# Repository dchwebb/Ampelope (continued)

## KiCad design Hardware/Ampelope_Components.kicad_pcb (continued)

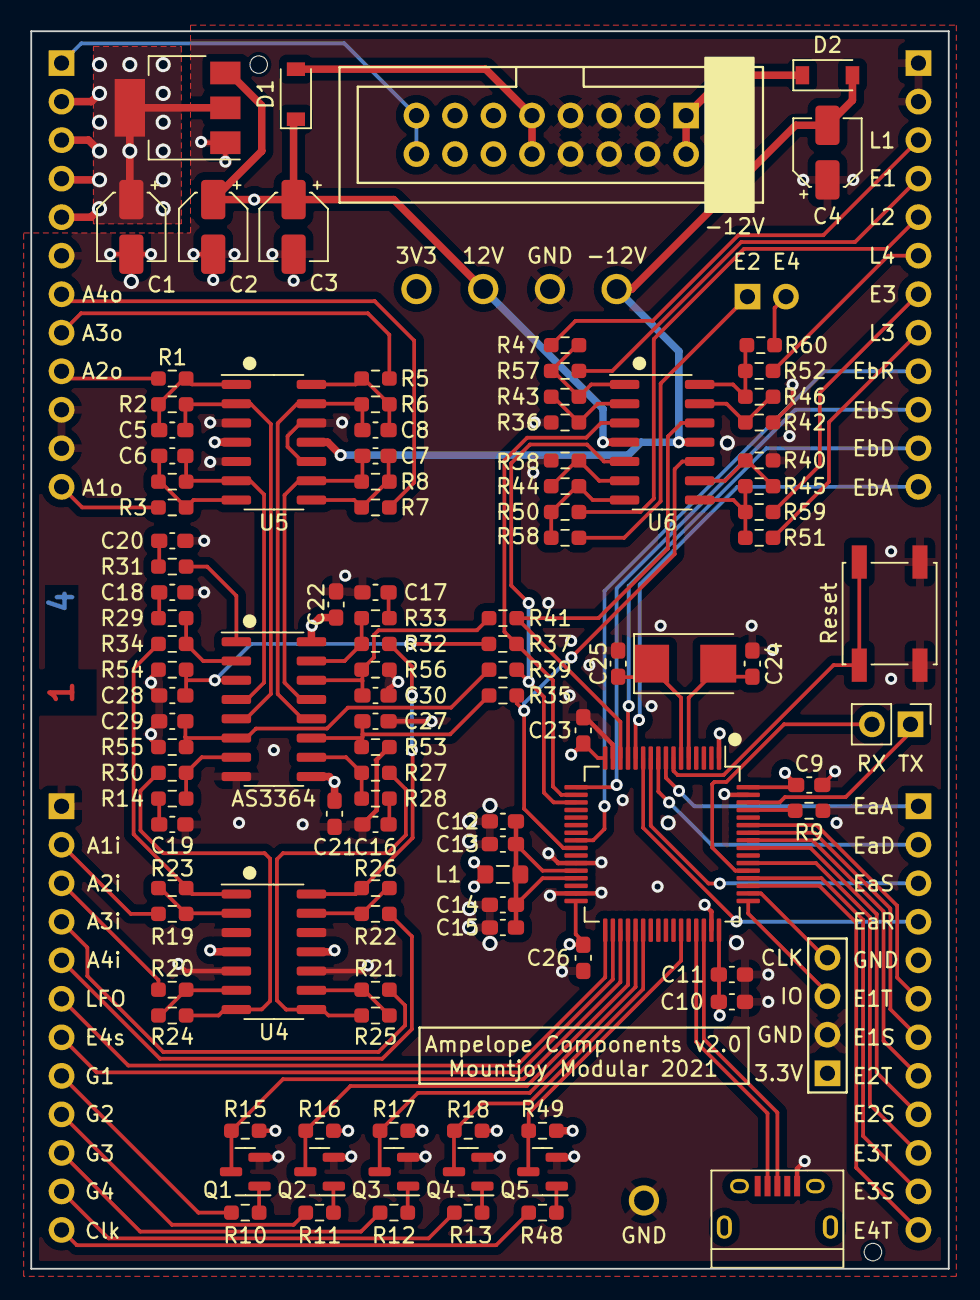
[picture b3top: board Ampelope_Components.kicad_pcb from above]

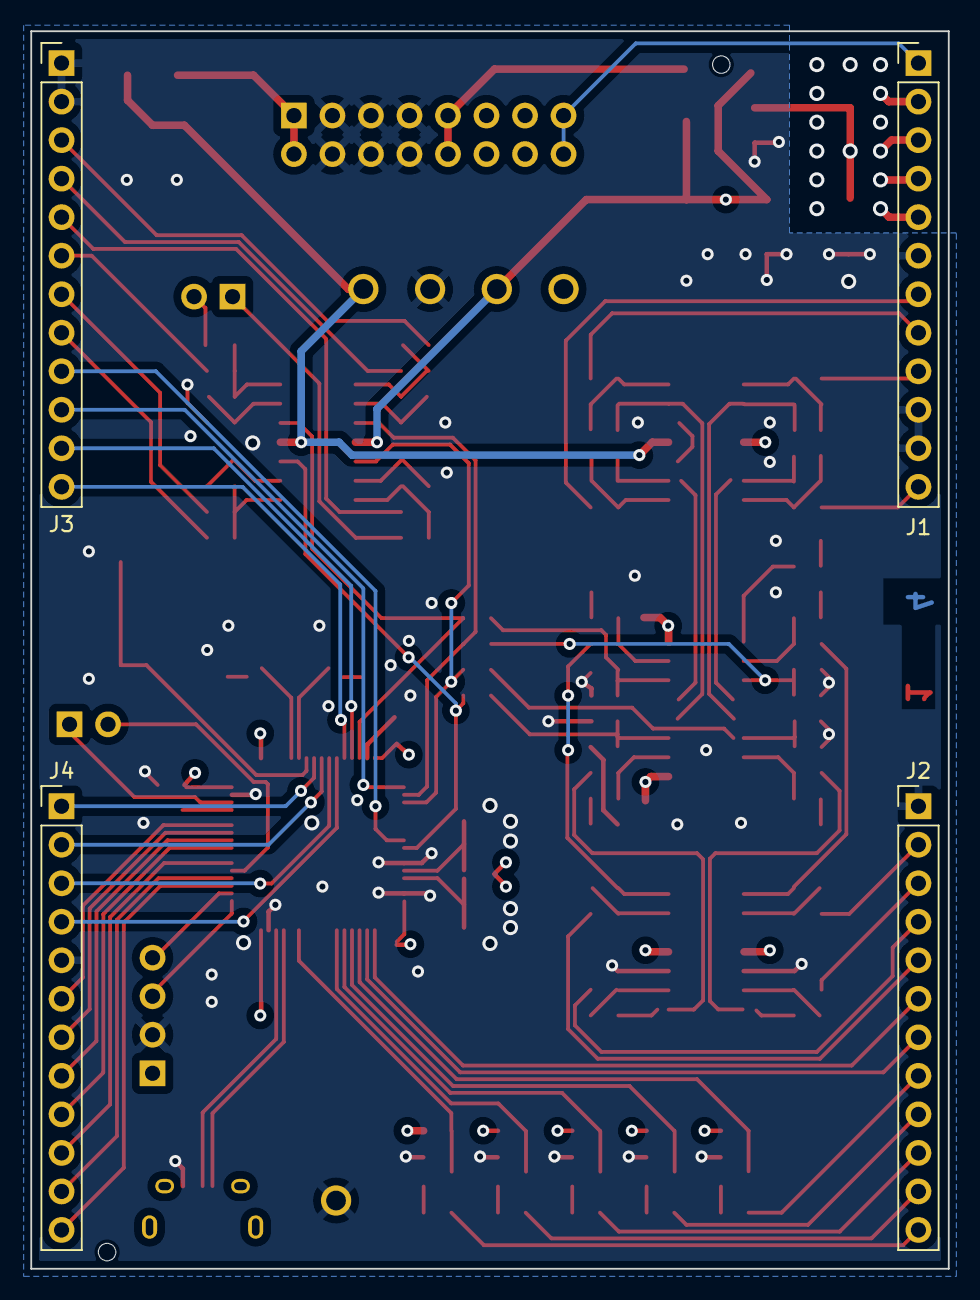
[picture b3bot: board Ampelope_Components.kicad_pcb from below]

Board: 4 copper layers, 60.5 x 81.6 mm, 123 parts (4 on the bottom side), 108 nets.

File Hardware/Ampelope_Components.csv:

"Source:","D:\Eurorack\Ampelope\Hardware\Ampelope_Components.kicad_sch"
"Date:","22/09/2021 17:17:07"
"Tool:","Eeschema (5.99.0-12348-g4b436fb86d)"
"Generator:","C:\Program Files\KiCad\5.99\bin\scripting\plugins/bom_csv_grouped_by_value_with_fp.py"
"Component Count:","121"
"Ref","Qnty","Value","Cmp name","Footprint","Description","Vendor"
"C1, C2, C3, C4, ","4","22uF","CP_Small","Capacitor_SMD:CP_Elec_4x5.8","Polarized capacitor, small symbol",""
"C5, C6, C7, C8, ","4","100pF","C_Small","Capacitor_SMD:C_0603_1608Metric_Pad1.08x0.95mm_HandSolder","Unpolarized capacitor, small symbol",""
"C9, C11, C13, C21, C22, C23, C26, ","7","100nF","C_Small","Capacitor_SMD:C_0603_1608Metric_Pad1.08x0.95mm_HandSolder","Unpolarized capacitor, small symbol",""
"C10, ","1","4.7uF","C_Small","Capacitor_SMD:C_0603_1608Metric_Pad1.08x0.95mm_HandSolder","Unpolarized capacitor, small symbol",""
"C12, C15, ","2","1uF","C_Small","Capacitor_SMD:C_0603_1608Metric_Pad1.08x0.95mm_HandSolder","Unpolarized capacitor, small symbol",""
"C14, C20, ","2","10nF","C_Small","Capacitor_SMD:C_0603_1608Metric_Pad1.08x0.95mm_HandSolder","Unpolarized capacitor, small symbol",""
"C16, C17, C18, C19, ","4","560pF","C_Small","Capacitor_SMD:C_0603_1608Metric_Pad1.08x0.95mm_HandSolder","Unpolarized capacitor, small symbol",""
"C24, C25, ","2","30pF","C_Small","Capacitor_SMD:C_0603_1608Metric_Pad1.08x0.95mm_HandSolder","Unpolarized capacitor, small symbol",""
"C27, C28, C29, C30, ","4","2.2nF","C_Small","Capacitor_SMD:C_0603_1608Metric_Pad1.08x0.95mm_HandSolder","Unpolarized capacitor, small symbol",""
"D1, D2, ","2","1N5819","1N5819","Diode_SMD:D_SOD-123","40V 1A Schottky Barrier Rectifier Diode, DO-41",""
"FID1, ","1","4_Layer_Marker","Fiducial","Custom_Footprints:4_Layer_Markers","Fiducial Marker",""
"J1, J2, J3, J4, ","4","Conn_01x12_Male","Conn_01x12_Male","Connector_PinHeader_2.54mm:PinHeader_1x12_P2.54mm_Vertical","Generic connector, single row, 01x12, script generated (kicad-library-utils/schlib/autogen/connector/)",""
"J5, ","1","Eurorack_16_pin_power","Eurorack_16_pin_power","Custom_Footprints:Eurorack_16_pin_header","",""
"J6, J9, ","2","Conn_01x02_Male","Conn_01x02_Male","Connector_PinHeader_2.54mm:PinHeader_1x02_P2.54mm_Vertical","Generic connector, single row, 01x02, script generated (kicad-library-utils/schlib/autogen/connector/)",""
"J7, ","1","SWD_Header","Conn_01x04_Male","Custom_Footprints:SWD_header","Generic connector, single row, 01x04, script generated (kicad-library-utils/schlib/autogen/connector/)",""
"J8, ","1","USB_B_Micro","USB_B_Micro","Custom_Footprints:USB_Micro-B_Amphenol","USB Micro Type B connector",""
"L1, ","1","L_Small","L_Small","Inductor_SMD:L_0805_2012Metric_Pad1.05x1.20mm_HandSolder","Inductor, small symbol",""
"Q1, Q2, Q3, Q4, Q5, ","5","MMBT3906","MMBT3906","Package_TO_SOT_SMD:SOT-23","-0.2A Ic, -40V Vce, Small Signal PNP Transistor, SOT-23",""
"R1, R3, R5, R7, R47, R50, R51, R52, R57, R58, R59, R60, ","12","1k","R_Small","Resistor_SMD:R_0603_1608Metric_Pad0.98x0.95mm_HandSolder","Resistor, small symbol",""
"R2, R4, R6, R8, R27, R30, R32, R34, ","8","30k","R_Small","Resistor_SMD:R_0603_1608Metric_Pad0.98x0.95mm_HandSolder","Resistor, small symbol",""
"R9, ","1","100k","R_Small","Resistor_SMD:R_0603_1608Metric_Pad0.98x0.95mm_HandSolder","Resistor, small symbol",""
"R10, R11, R12, R13, R15, R16, R17, R18, R43, R44, R45, R46, R48, R49, ","14","4k7","R_Small","Resistor_SMD:R_0603_1608Metric_Pad0.98x0.95mm_HandSolder","Resistor, small symbol",""
"R14, R28, R29, R33, ","4","510R","R_Small","Resistor_SMD:R_0603_1608Metric_Pad0.98x0.95mm_HandSolder","Resistor, small symbol",""
"R19, R20, R21, R22, R23, R24, R25, R26, R53, R54, R55, R56, ","12","10k","R_Small","Resistor_SMD:R_0603_1608Metric_Pad0.98x0.95mm_HandSolder","Resistor, small symbol",""
"R31, ","1","100R","R_Small","Resistor_SMD:R_0603_1608Metric_Pad0.98x0.95mm_HandSolder","Resistor, small symbol",""
"R35, R37, R39, R41, ","4","6k8","R_Small","Resistor_SMD:R_0603_1608Metric_Pad0.98x0.95mm_HandSolder","Resistor, small symbol",""
"R36, R38, R40, R42, ","4","3k3","R_Small","Resistor_SMD:R_0603_1608Metric_Pad0.98x0.95mm_HandSolder","Resistor, small symbol",""
"RESET1, ","1","SW_Push","SW_Push","Custom_Footprints:SW_SPST_EVQQ2","Push button switch, generic, two pins",""
"TP1, TP2, TP3, TP4, TP5, ","5","TestPoint","TestPoint","Custom_Footprints:1.3mm_Test_Point","test point",""
"U1, ","1","STM32G431RB","STM32G431RB","Package_QFP:LQFP-64_10x10mm_P0.5mm","ARM Cortex-M4 MCU, 128KB flash, 32KB RAM, 170MHz, 1.8-3.6V, 50 GPIO, LQFP-64",""
"U2, ","1","AS3364","SSI2164","Package_SO:SOIC-16_3.9x9.9mm_P1.27mm","Quad VCA, SOIC-16",""
"U3, ","1","LM1117-3.3","LM1117-3.3","Package_TO_SOT_SMD:SOT-223-3_TabPin2","800mA Low-Dropout Linear Regulator, 3.3V fixed output, TO-220/TO-252/TO-263/SOT-223",""
"U4, U5, U6, ","3","TL074","TL074","Package_SO:SOIC-14_3.9x8.7mm_P1.27mm","Quad Low-Noise JFET-Input Operational Amplifiers, DIP-14/SOIC-14",""
"Y1, ","1","8MHz 20pF","Crystal","Crystal:Crystal_SMD_0603-2Pin_6.0x3.5mm","Two pin crystal",""

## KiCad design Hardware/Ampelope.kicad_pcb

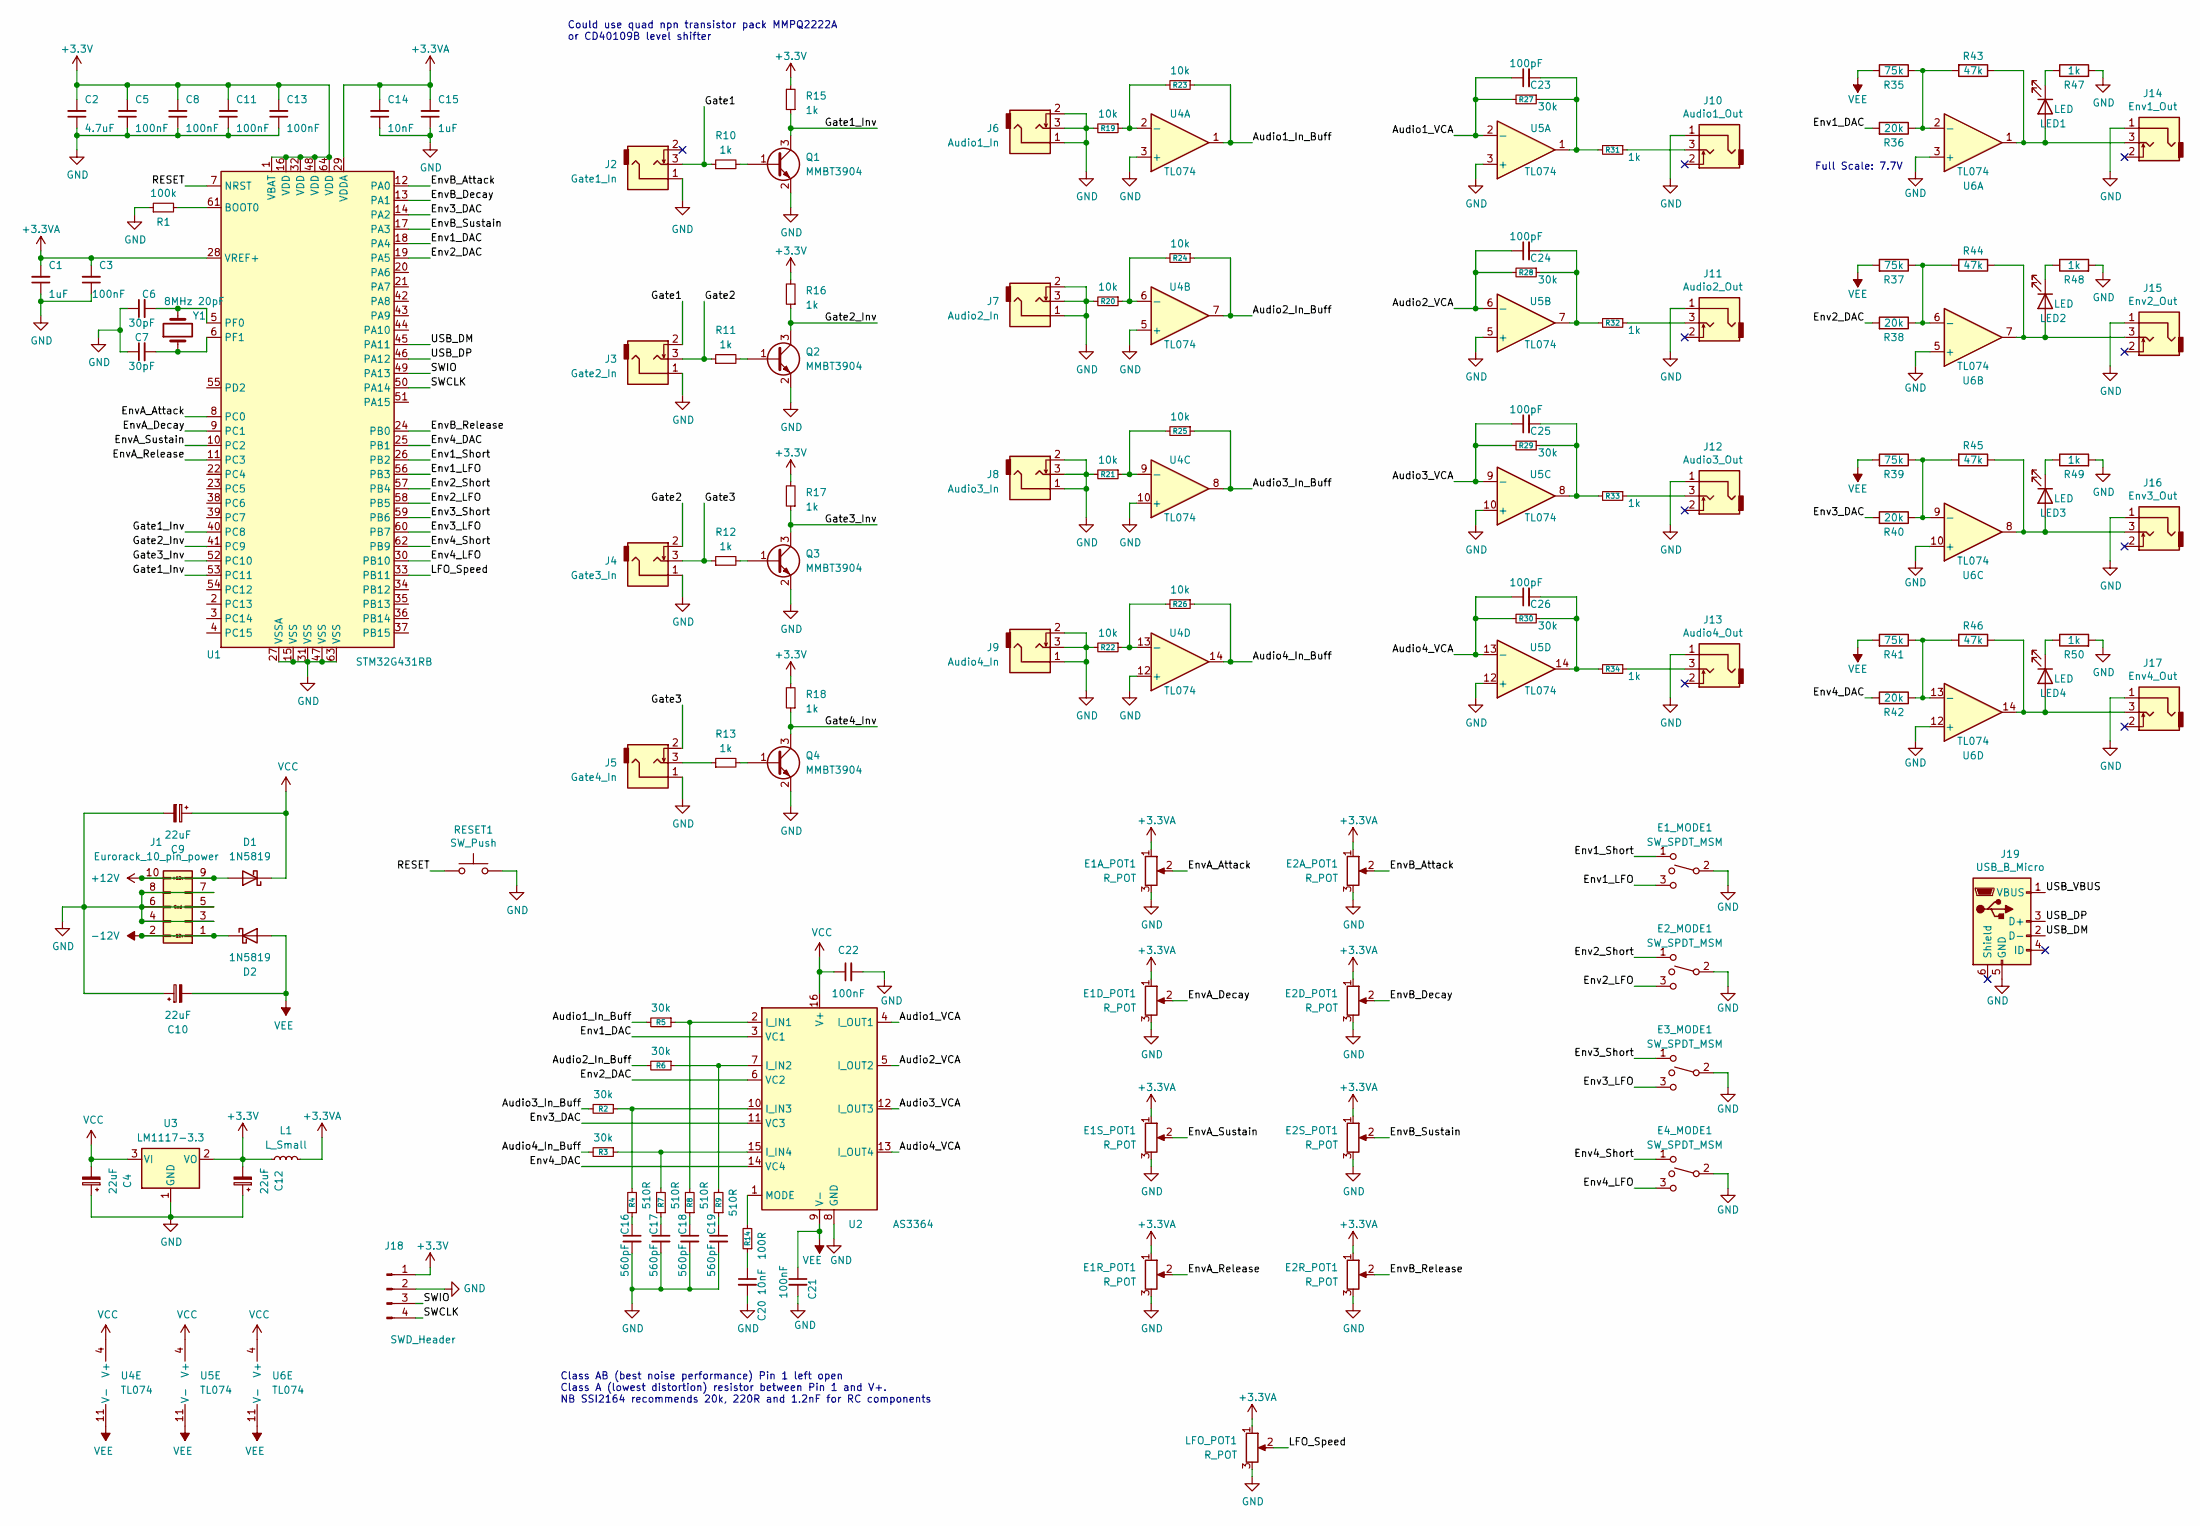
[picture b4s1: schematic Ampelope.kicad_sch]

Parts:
C1, C15: 1uF; C_0603_1608Metric_Pad1.08x0.95mm_HandSolder
C2: 4.7uF; C_0603_1608Metric_Pad1.08x0.95mm_HandSolder
C3, C5, C8, C11, C13: 100nF; C_0603_1608Metric_Pad1.08x0.95mm_HandSolder
C4, C9, C10, C12: 22uF; CP_Elec_4x5.8
C6, C7: 30pF; C_0603_1608Metric_Pad1.08x0.95mm_HandSolder
C14: 10nF; C_0603_1608Metric_Pad1.08x0.95mm_HandSolder
C16, C17, C18, C19: 560pF; C_0603_1608Metric_Pad1.08x0.95mm_HandSolder; Part_Number C84721
C20: 10nF; C_0603_1608Metric_Pad1.08x0.95mm_HandSolder; Part_Number C57112
C21, C22: 100nF; C_0603_1608Metric_Pad1.08x0.95mm_HandSolder; Part_Number C84721
C23, C24, C25, C26: 100pF; C_0603_1608Metric_Pad1.08x0.95mm_HandSolder
D1, D2: 1N5819; D_SOD-123
E1A_POT1, E1D_POT1, E1R_POT1, E1S_POT1, E2A_POT1, E2D_POT1, E2R_POT1, E2S_POT1: R_POT; Alpha_9mm_Potentiometer_Aligned
E1_MODE1, E2_MODE1, E3_MODE1, E4_MODE1: SW_SPDT_MSM; SPDT_SubMiniature_Aligned
J1: Eurorack_10_pin_power; Eurorack_10_pin_header
J2: Gate1_In; THONKICONN_hole
J3: Gate2_In; THONKICONN_hole
J4: Gate3_In; THONKICONN_hole
J5: Gate4_In; THONKICONN_hole
J6: Audio1_In; THONKICONN_hole
J7: Audio2_In; THONKICONN_hole
J8: Audio3_In; THONKICONN_hole
J9: Audio4_In; THONKICONN_hole
J10: Audio1_Out; THONKICONN_hole
J11: Audio2_Out; THONKICONN_hole
J12: Audio3_Out; THONKICONN_hole
J13: Audio4_Out; THONKICONN_hole
J14: Env1_Out; THONKICONN_hole
J15: Env2_Out; THONKICONN_hole
J16: Env3_Out; THONKICONN_hole
J17: Env4_Out; THONKICONN_hole
J18: SWD_Header; SWD_header
J19: USB_B_Micro; USB_Micro-B_Amphenol
L1: L_Small; L_0805_2012Metric_Pad1.05x1.20mm_HandSolder
LED1, LED2, LED3, LED4: LED; LED_D3.0mm
LFO_POT1: R_POT; Alpha_9mm_Potentiometer_Aligned
Q1, Q2, Q3, Q4: MMBT3904; SOT-23
R1: 100k; R_0603_1608Metric_Pad0.98x0.95mm_HandSolder
R2, R3, R5, R6, R27, R28, R29, R30: 30k; R_0603_1608Metric_Pad0.98x0.95mm_HandSolder; Part_Number C22984
R4, R7, R8, R9: 510R; R_0603_1608Metric_Pad0.98x0.95mm_HandSolder; Part_Number C23193
R10, R11, R12, R13, R15, R16, R17, R18: 1k; R_0603_1608Metric_Pad0.98x0.95mm_HandSolder
R14: 100R; R_0603_1608Metric_Pad0.98x0.95mm_HandSolder; Part_Number C22775
R19, R20, R21, R22, R23, R24, R25, R26: 10k; R_0603_1608Metric_Pad0.98x0.95mm_HandSolder; Part_Number C22984
R31, R32, R33, R34: 1k; R_0603_1608Metric_Pad0.98x0.95mm_HandSolder; Part_Number C22984
R35, R37, R39, R41: 75k; R_0603_1608Metric_Pad0.98x0.95mm_HandSolder; Part_Number C23231
R36, R38, R40, R42: 20k; R_0603_1608Metric_Pad0.98x0.95mm_HandSolder; Part_Number C25803
R43, R44, R45, R46: 47k; R_0603_1608Metric_Pad0.98x0.95mm_HandSolder; Part_Number C25819
R47, R48, R49, R50: 1k; R_0603_1608Metric_Pad0.98x0.95mm_HandSolder; Part_Number C25819
RESET1: SW_Push; SW_PUSH_6mm_aligned
U1: STM32G431RB; LQFP-64_10x10mm_P0.5mm
U2: AS3364; SOIC-16_3.9x9.9mm_P1.27mm
U3: LM1117-3.3; SOT-223-3_TabPin2
U4, U5, U6: TL074; SOIC-14_3.9x8.7mm_P1.27mm
Y1: 8MHz 20pF; Crystal_SMD_5032-2Pin_5.0x3.2mm_HandSoldering; Part_Number C115962

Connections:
+3.3VA: C1.2, C3.2, C14.2, C15.2, E1A_POT1.1, E1D_POT1.1, E1R_POT1.1, E1S_POT1.1, E2A_POT1.1, E2D_POT1.1, E2R_POT1.1, E2S_POT1.1, L1.2, LFO_POT1.1, U1.28 (VREF+), U1.29 (VDDA)
+3V3: C2.2, C5.2, C8.2, C11.2, C12.2, C13.2, J18.1, L1.1, R15.2, R16.2, R17.2, R18.2, U1.1 (VBAT), U1.16 (VDD), U1.32 (VDD), U1.48 (VDD), U1.64 (VDD), U3.2 (VO)
+12V: D1.2 (A), J1.9, J1.10
-12V: D2.1 (K), J1.1, J1.2
/Audio1_In_Buff: R5.2, R23.1, U4.1
/Audio1_VCA: C23.1, R27.2, U2.4 (I_OUT1), U5.2 (-)
/Audio2_In_Buff: R6.2, R24.1, U4.7
/Audio2_VCA: C24.1, R28.2, U2.5 (I_OUT2), U5.6 (-)
/Audio3_In_Buff: R2.2, R25.1, U4.8
/Audio3_VCA: C25.1, R29.2, U2.12 (I_OUT3), U5.9 (-)
/Audio4_In_Buff: R3.2, R26.1, U4.14
/Audio4_VCA: C26.1, R30.2, U2.13 (I_OUT4), U5.13 (-)
/Env1_DAC: R36.2, U1.18 (PA4), U2.3 (VC1)
/Env1_LFO: E1_MODE1.3, U1.56 (PB3)
/Env1_Short: E1_MODE1.1, U1.26 (PB2)
/Env2_DAC: R38.2, U1.19 (PA5), U2.6 (VC2)
/Env2_LFO: E2_MODE1.3, U1.58 (PB5)
/Env2_Short: E2_MODE1.1, U1.57 (PB4)
/Env3_DAC: R40.2, U1.14 (PA2), U2.11 (VC3)
/Env3_LFO: E3_MODE1.3, U1.60 (PB7)
/Env3_Short: E3_MODE1.1, U1.59 (PB6)
/Env4_DAC: R42.2, U1.25 (PB1), U2.14 (VC4)
/Env4_LFO: E4_MODE1.3, U1.30 (PB10)
/Env4_Short: E4_MODE1.1, U1.62 (PB9)
/EnvA_Attack: E1A_POT1.2, U1.8 (PC0)
/EnvA_Decay: E1D_POT1.2, U1.9 (PC1)
/EnvA_Release: E1R_POT1.2, U1.11 (PC3)
/EnvA_Sustain: E1S_POT1.2, U1.10 (PC2)
/EnvB_Attack: E2A_POT1.2, U1.12 (PA0)
/EnvB_Decay: E2D_POT1.2, U1.13 (PA1)
/EnvB_Release: E2R_POT1.2, U1.24 (PB0)
/EnvB_Sustain: E2S_POT1.2, U1.17 (PA3)
/Gate1: J2.3, J3.2, R10.1
/Gate1_Inv: Q1.3 (C), R15.1, U1.40 (PC8), U1.53 (PC11)
/Gate2: J3.3, J4.2, R11.1
/Gate2_Inv: Q2.3 (C), R16.1, U1.41 (PC9)
/Gate3: J4.3, J5.2, R12.1
/Gate3_Inv: Q3.3 (C), R17.1, U1.52 (PC10)
/Gate4_Inv: Q4.3 (C), R18.1
/LFO_Speed: LFO_POT1.2, U1.33 (PB11)
/RESET: RESET1.1, U1.7 (NRST)
/SWCLK: J18.4, U1.50 (PA14)
/SWIO: J18.3, U1.49 (PA13)
/USB_DM: J19.2 (D-), U1.45 (PA11)
/USB_DP: J19.3 (D+), U1.46 (PA12)
/USB_VBUS: J19.1 (VBUS)
GND: C1.1, C2.1, C3.1, C4.1, C5.1, C6.1, C7.1, C8.1, C9.2, C10.1, C11.1, C12.1, C13.1, C14.1, C15.1, C16.2, C17.2, C18.2, C19.2, C20.2, C21.2, C22.2, E1A_POT1.3, E1D_POT1.3, E1R_POT1.3, E1S_POT1.3, E1_MODE1.2, E2A_POT1.3, E2D_POT1.3, E2R_POT1.3, E2S_POT1.3, E2_MODE1.2, E3_MODE1.2, E4_MODE1.2, J1.3, J1.4, J1.5, J1.6, J1.7, J1.8, J2.1, J3.1, J4.1, J5.1, J6.1, J6.2, J6.3, J7.1, J7.2, J7.3, J8.1, J8.2, J8.3, J9.1, J9.2, J9.3, J10.1, J11.1, J12.1, J13.1, J14.1, J15.1, J16.1, J17.1, J18.2, J19.5 (GND), LFO_POT1.3, Q1.2 (E), Q2.2 (E), Q3.2 (E), Q4.2 (E), R1.1, R19.2, R20.2, R21.2, R22.2, R47.2, R48.2, R49.2, R50.2, RESET1.2, U1.15 (VSS), U1.27 (VSSA), U1.31 (VSS), U1.47 (VSS), U1.63 (VSS), U2.8 (GND), U3.1 (GND), U4.3 (+), U4.5 (+), U4.10 (+), U4.12 (+), U5.3 (+), U5.5 (+), U5.10 (+), U5.12 (+), U6.3 (+), U6.5 (+), U6.10 (+), U6.12 (+)
unnamed: C6.2, U1.5 (PF0), Y1.2
unnamed: C7.2, U1.6 (PF1), Y1.1
unnamed: C16.1, R4.1
unnamed: C17.1, R7.1
unnamed: C18.1, R8.1
unnamed: C19.1, R9.1
unnamed: C20.1, R14.1
unnamed: C23.2, R27.1, R31.2, U5.1
unnamed: C24.2, R28.1, R32.2, U5.7
unnamed: C25.2, R29.1, R33.2, U5.8
unnamed: C26.2, R30.1, R34.2, U5.14
unnamed: J5.3, R13.1
unnamed: J10.3, R31.1
unnamed: J11.3, R32.1
unnamed: J12.3, R33.1
unnamed: J13.3, R34.1
unnamed: LED1.1 (K), R47.1
unnamed: J14.3, LED1.2 (A), R43.1, U6.1
unnamed: LED2.1 (K), R48.1
unnamed: J15.3, LED2.2 (A), R44.1, U6.7
unnamed: LED3.1 (K), R49.1
unnamed: J16.3, LED3.2 (A), R45.1, U6.8
unnamed: LED4.1 (K), R50.1
unnamed: J17.3, LED4.2 (A), R46.1, U6.14
unnamed: Q1.1 (B), R10.2
unnamed: Q2.1 (B), R11.2
unnamed: Q3.1 (B), R12.2
unnamed: Q4.1 (B), R13.2
unnamed: R1.2, U1.61 (BOOT0)
unnamed: R2.1, R4.2, U2.10 (I_IN3)
unnamed: R3.1, R7.2, U2.15 (I_IN4)
unnamed: R5.1, R8.2, U2.2 (I_IN1)
unnamed: R6.1, R9.2, U2.7 (I_IN2)
unnamed: R14.2, U2.1 (MODE)
unnamed: R19.1, R23.2, U4.2 (-)
unnamed: R20.1, R24.2, U4.6 (-)
unnamed: R21.1, R25.2, U4.9 (-)
unnamed: R22.1, R26.2, U4.13 (-)
unnamed: R35.1, R36.1, R43.2, U6.2 (-)
unnamed: R37.1, R38.1, R44.2, U6.6 (-)
unnamed: R39.1, R40.1, R45.2, U6.9 (-)
unnamed: R41.1, R42.1, R46.2, U6.13 (-)
VCC: C4.2, C9.1, C22.1, D1.1 (K), U2.16 (V+), U3.3 (VI), U4.4 (V+), U5.4 (V+), U6.4 (V+)
VEE: C10.2, C21.1, D2.2 (A), R35.2, R37.2, R39.2, R41.2, U2.9 (V-), U4.11 (V-), U5.11 (V-), U6.11 (V-)

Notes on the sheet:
Class AB (best noise performance) Pin 1 left open Class A (lowest distortion) resistor between Pin 1 and V+. NB SSI2164 recommends 20k, 220R and 1.2nF for RC components
Could use quad npn transistor pack MMPQ2222A or CD40109B level shifter
Full Scale: 7.7V

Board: 2 copper layers, 127 parts (0 on the bottom side), 90 nets, no tracks yet.

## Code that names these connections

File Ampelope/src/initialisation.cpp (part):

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
void InitDAC()
{
	// Configure 4 DAC outputs PA4 and PA5 are regular DAC1 buffered outputs; PA2 and PB1 are DAC3 via OpAmp1 and OpAmp3 (Manual p.789)

	RCC->AHB2ENR |= RCC_AHB2ENR_GPIOAEN;			// Enable GPIO Clock
	RCC->AHB2ENR |= RCC_AHB2ENR_GPIOBEN;			// Enable GPIO Clock
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	RCC->AHB2ENR |= RCC_AHB2ENR_DAC3EN;				// Enable DAC Clock

	DAC1->MCR &= ~DAC_MCR_MODE1_Msk;				// Set to normal mode: DAC channel1 is connected to external pin with Buffer enabled
	DAC1->CR |= DAC_CR_EN1;							// Enable DAC using PA4 (DAC_OUT1)

	DAC1->MCR &= ~DAC_MCR_MODE2_Msk;				// Set to normal mode: DAC channel2 is connected to external pin with Buffer enabled
	DAC1->CR |= DAC_CR_EN2;							// Enable DAC using PA5 (DAC_OUT2)

	// output triggered with DAC->DHR12R1 = x;

	// Opamp for DAC3 Channel 1: Follower configuration mode - output on PA2
	DAC3->MCR |= DAC_MCR_MODE1_0 | DAC_MCR_MODE1_1;	// 011: DAC channel1 is connected to on chip peripherals with Buffer disabled
	DAC3->CR |= DAC_CR_EN1;							// Enable DAC

	OPAMP1->CSR |= OPAMP_CSR_VMSEL;					// 11: Opamp_out connected to OPAMPx_VINM input
	OPAMP1->CSR |= OPAMP_CSR_VPSEL;					// 11: DAC3_CH1  connected to OPAMP1 VINP input
	OPAMP1->CSR |= OPAMP_CSR_OPAMPxEN;				// Enable OpAmp: voltage on pin OPAMPx_VINP is buffered to pin OPAMPx_VOUT (PA2)

	// Opamp for DAC3 Channel 2: Follower configuration mode - output on PB1
	// NB According to manual p.790 this should only work on category 3/4 devices and STM32G431 is category 2, but tested working
	DAC3->MCR |= DAC_MCR_MODE2_0 | DAC_MCR_MODE2_1;	// 011: DAC channel2 is connected to on chip peripherals with Buffer disabled
	DAC3->CR |= DAC_CR_EN2;							// Enable DAC

	OPAMP3->CSR |= OPAMP_CSR_VMSEL;					// 11: Opamp_out connected to OPAMPx_VINM input
	OPAMP3->CSR |= OPAMP_CSR_VPSEL;					// 11: DAC3_CH2  connected to OPAMP1 VINP input
	OPAMP3->CSR |= OPAMP_CSR_OPAMPxEN;				// Enable OpAmp: voltage on pin OPAMPx_VINP is buffered to pin OPAMPx_VOUT (PB1)

}

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	RCC->AHB2ENR |= RCC_AHB2ENR_GPIOBEN;			// reset and clock control - advanced high performance bus - GPIO port B
	RCC->AHB2ENR |= RCC_AHB2ENR_GPIOCEN;			// reset and clock control - advanced high performance bus - GPIO port C

	GPIOB->MODER &= ~GPIO_MODER_MODER13;			// configure PB13 gate 1 input
	GPIOB->MODER &= ~GPIO_MODER_MODER14;			// configure PB14 gate 2 input
	GPIOB->MODER &= ~GPIO_MODER_MODER15;			// configure PB15 gate 3 input
	GPIOC->MODER &= ~GPIO_MODER_MODER6;				// configure PC6  gate 4 input

	// NB PB6 is used in USB Power delivery and by default has a pull down to ground - disable in the PWR register (datasheet p.60 note 5)
	PWR->CR3 |= PWR_CR3_UCPD_DBDIS;

	GPIOB->MODER &= ~GPIO_MODER_MODER5;				// configure PB5  Env 1 Short input
	GPIOB->MODER &= ~GPIO_MODER_MODER6;				// configure PB6  Env 1 tremolo input*
	GPIOB->MODER &= ~GPIO_MODER_MODER3;				// configure PB3  Env 2 Short input
	GPIOB->MODER &= ~GPIO_MODER_MODER4;				// configure PB4  Env 2 tremolo input
	GPIOC->MODER &= ~GPIO_MODER_MODER10;			// configure PC10 Env 3 Short input
	GPIOC->MODER &= ~GPIO_MODER_MODER12;			// configure PC12 Env 3 tremolo input
	GPIOB->MODER &= ~GPIO_MODER_MODER12;			// configure PB12 Env 4 Short input
	GPIOA->MODER &= ~GPIO_MODER_MODER15;			// configure PA15 Env 4 tremolo input

	GPIOB->PUPDR |= GPIO_PUPDR_PUPDR5_0;			// configure PB5  Env 1 Pull-up
	GPIOB->PUPDR |= GPIO_PUPDR_PUPDR6_0;			// configure PB6  Env 1 Pull-up
	GPIOB->PUPDR |= GPIO_PUPDR_PUPDR3_0;			// configure PB3  Env 2 Pull-up
	GPIOB->PUPDR |= GPIO_PUPDR_PUPDR4_0;			// configure PB4  Env 2 Pull-up
	GPIOC->PUPDR |= GPIO_PUPDR_PUPDR10_0;			// configure PC10 Env 3 Pull-up
	GPIOC->PUPDR |= GPIO_PUPDR_PUPDR12_0;			// configure PC12 Env 3 Pull-up
	GPIOB->PUPDR |= GPIO_PUPDR_PUPDR12_0;			// configure PB12 Env 4 Pull-up
	GPIOA->PUPDR |= GPIO_PUPDR_PUPDR15_0;			// configure PA15 Env 4 Pull-up

	GPIOA->MODER &= ~GPIO_MODER_MODER9;				// configure PA9 clock input
	GPIOB->MODER &= ~GPIO_MODER_MODER9_1;			// configure PB9 debug out
}


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
	/*--------------------------------------------------------------------------------------------
	Configure ADC Channels to be converted:
	0	PC0 ADC12_IN6		Env1 Attack
	1	PC1 ADC12_IN7		Env1 Decay
	2	PC2 ADC12_IN8		Env1 Sustain
	3	PC3 ADC12_IN9		Env1 Release

	4	PA0 ADC12_IN1		Env2 Attack
	5	PA1 ADC12_IN2		Env2 Decay
	6	PA3 ADC1_IN4		Env2 Sustain
	7	PB0 ADC1_IN15		Env2 Release

	8	PB11 ADC12_IN14		LFO Speed
	*/

	InitAdcPins(ADC1, {6, 7, 8, 9, 1, 2, 4, 15, 14});
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
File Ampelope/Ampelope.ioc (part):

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Mcu.Name=STM32G431R(6-8-B)Tx
Mcu.Package=LQFP64
Mcu.UserName=STM32G431RBTx
PA1.Mode=Follower
PA1.Signal=OPAMP3_VINP
PA13.GPIOParameters=GPIO_Label
PA13.GPIO_Label=T_SWDIO
PA13.Signal=SYS_JTMS-SWDIO
PA14.GPIOParameters=GPIO_Label
PA14.GPIO_Label=T_SWCLK
PA14.Signal=SYS_JTCK-SWCLK
PA2.GPIOParameters=GPIO_Label
PA2.GPIO_Label=LPUART1_TX [STLINKV3E_VCP_RX]
PA2.Signal=LPUART1_TX
PA3.GPIOParameters=GPIO_Label
PA3.GPIO_Label=LPUART1_RX [STLINKV3E_VCP_TX]
PA3.Signal=LPUART1_RX
PA4.Signal=COMP_DAC11_group
PA5.GPIOParameters=GPIO_Label
PA5.GPIO_Label=LD2 [green]
PA5.Signal=GPIO_Output
PB1.Mode=Follower
PB1.Signal=OPAMP3_VOUT
PB3.GPIOParameters=GPIO_Label
PB3.GPIO_Label=T_SWO
PB3.Signal=SYS_JTDO-SWO
PC13.GPIOParameters=GPIO_Label
PC13.GPIO_Label=B1 [blue push button]
PC13.Signal=GPXTI13
PC14-OSC32_IN.Signal=RCC_OSC32_IN
PC15-OSC32_OUT.Signal=RCC_OSC32_OUT
PC4.Mode=Half_duplex(single_wire_mode)
PC4.Signal=USART1_TX
PF0-OSC_IN.Mode=HSE-External-Oscillator
PF0-OSC_IN.Signal=RCC_OSC_IN
PF1-OSC_OUT.Mode=HSE-External-Oscillator
PF1-OSC_OUT.Signal=RCC_OSC_OUT
RCC.HSE_VALUE=8000000
RCC.SYSCLKFreq_VALUE=170000000
RCC.SYSCLKSource=RCC_SYSCLKSOURCE_PLLCLK
board=NUCLEO-G431RB
boardIOC=true

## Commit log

2021-06-23 Added STM32G431 project; clock configuration complete
2021-06-25 Started adding Systick and DAC to initialisation
2021-07-03 Started implementing ADSR Code
2021-07-05 Started schematic; basic envelope working on timer
2021-07-08 ADC and DMA configured and working
2021-07-09 DAC3 via internal OpAmp connected to PA2 - working
2021-07-09 Added additional DAC/Opamp channel
2021-07-14 Started implementing USB peripheral control
2021-07-15 Further USB work - setup packet decoded
2021-07-15 Started implementing USB RX interrupt
2021-07-16 Working up to set address (though issues with DATA0/1 toggling)
2021-07-17 More work on USB - trying to fix issues with EP0R values
2021-07-18 USB Set address response working
2021-07-18 USB Addressing now working
2021-07-19 Added UART Handler for debugging
2021-07-19 Starting setting up USB debug output via Nucleo UART/user button
2021-07-22 USB cleanup
2021-07-22 Fixed bug: working up to stage of split transfer
2021-07-22 Handling large split packets; descriptor phase completes
2021-07-23 Started adding CDC initialisation
2021-07-25 Started implementing Activate Endpoint
2021-07-26 Endpoint setup routine written
2021-07-29 USB Serial receive working (not fully tested)
2021-07-30 Improvements to CDC line coding routine
2021-07-30 Some clean-up of the USB class
2021-07-31 Basic send and receive working
2021-07-31 Fixed sending and receiving long strings
2021-07-31 USB Class code clean up
2021-08-01 More code clean up; fixed issue disconnecting and reconnecting USB
2021-08-01 Macro clean up; fixed issue receiving large packets
2021-08-02 More clean up; tested working on Ubuntu Linux and alternative Windows 10 laptop
2021-08-02 Refactoring and code clean up; extra information added to debug output
2021-08-03 More code clean up; improved debug data
2021-08-03 More clean up
2021-08-05 More USB Clean Up
2021-08-06 Fixed bug transmitting USB buffer whose size is a multiple of 64
2021-08-09 Starting modelling attack curves from Roland clone ADSR
2021-08-09 ADSR decay phase modelled
2021-08-10 Fixed very slow performance and updated attack magic numbers to compensate
2021-08-11 Disabled USB Debug; timings modified to use seconds
2021-08-13 Updated envelope model for full ADSR, long and short times
2021-08-16 Added additional ADC channels for Envelope 1 ADSR controls
2021-08-16 Envelope 1 with VCA working; schematic updated
2021-08-18 Added some test code to use CORDIC peripheral to generate a sine wave to modulate VCA
2021-08-19 More CORDIC tests; schematic updates
2021-08-20 Work on exponential approximation function (lookup)
2021-08-22 Experiments using CORDIC to calculate exponentials and ln
2021-08-22 Cleaned up CORDIC exponent function
2021-08-23 Performance improvements calculating ADSR values; mainly using CORDIC to generate exponentials
2021-08-23 Attack and decay phases fully optimised (sub 1uS)
2021-08-23 Release optimised; smoothed attack control; updated LFO
2021-08-27 Added power supply components to schematic
2021-08-27 Duplicated IO for all four envelopes/VCAs
2021-08-28 Added switches and poteniometers to schematic
2021-08-28 More work on schematic
2021-08-29 Preliminary pcb layout preparation
2021-08-30 Split PCBs into separate control and component boards
2021-08-31 First Draft Layout of controls PCB
2021-09-01 Started rough placement of component board
2021-09-01 More layout of component board
2021-09-01 More layout on component board
2021-09-02 More component layout
2021-09-04 Formatting clean up
2021-09-04 Draft of panel layout
2021-09-05 Work on panel and control layout
2021-09-06 First draft of panel and control boards complete
2021-09-07 Layout on component board
2021-09-08 Component layout refinement; pre change of input protection transistors to PNPs
2021-09-09 Updated to work correctly with AS3364 (gain levels, non inverting etc)
2021-09-09 Updates to component PCB to reflect VCA schematic changes
2021-09-11 Added test points to component PCB; Added 3D mockups
2021-09-11 Wired up control board
2021-09-11 Fixed DRC errors on control and component boards
2021-09-13 Code to start testing tremolo clock circuit
2021-09-14 Tremolo can be clock synched; increased accuracy of CORDIC exp calculation to fix bug w long releases
2021-09-15 Various schematic and PCB tidying
2021-09-16 Minor PCB cleanup
2021-09-18 Further PCB tidy up and DAC testing
2021-09-23 Changed input protection diodes back to 3904s; prepared gerbers
2021-09-23 Prepared gerbers for pcb manufacture
2021-10-09 Fixes to component schematic and pcb (power supply and silkscreen); Firmware updated to use correct pin assignments
2021-10-09 Independent settings for all 4 envelopes implemented
2021-10-11 Added Readme and pictures
2021-10-12 Various bug fixes and code tidying
2021-10-12 Tremolo clocking working correctly with multipliers
2021-10-13 Tidied up debug commands
2022-03-14 Updated to Kicad v6
2023-03-01 Created Adapter Board to break out Quad signals
2023-03-02 Fixes to Adapter Board
2023-03-03 Added dummy connector
2023-06-23 Update adc naming conventions
2025-06-23 Added firmware build files
